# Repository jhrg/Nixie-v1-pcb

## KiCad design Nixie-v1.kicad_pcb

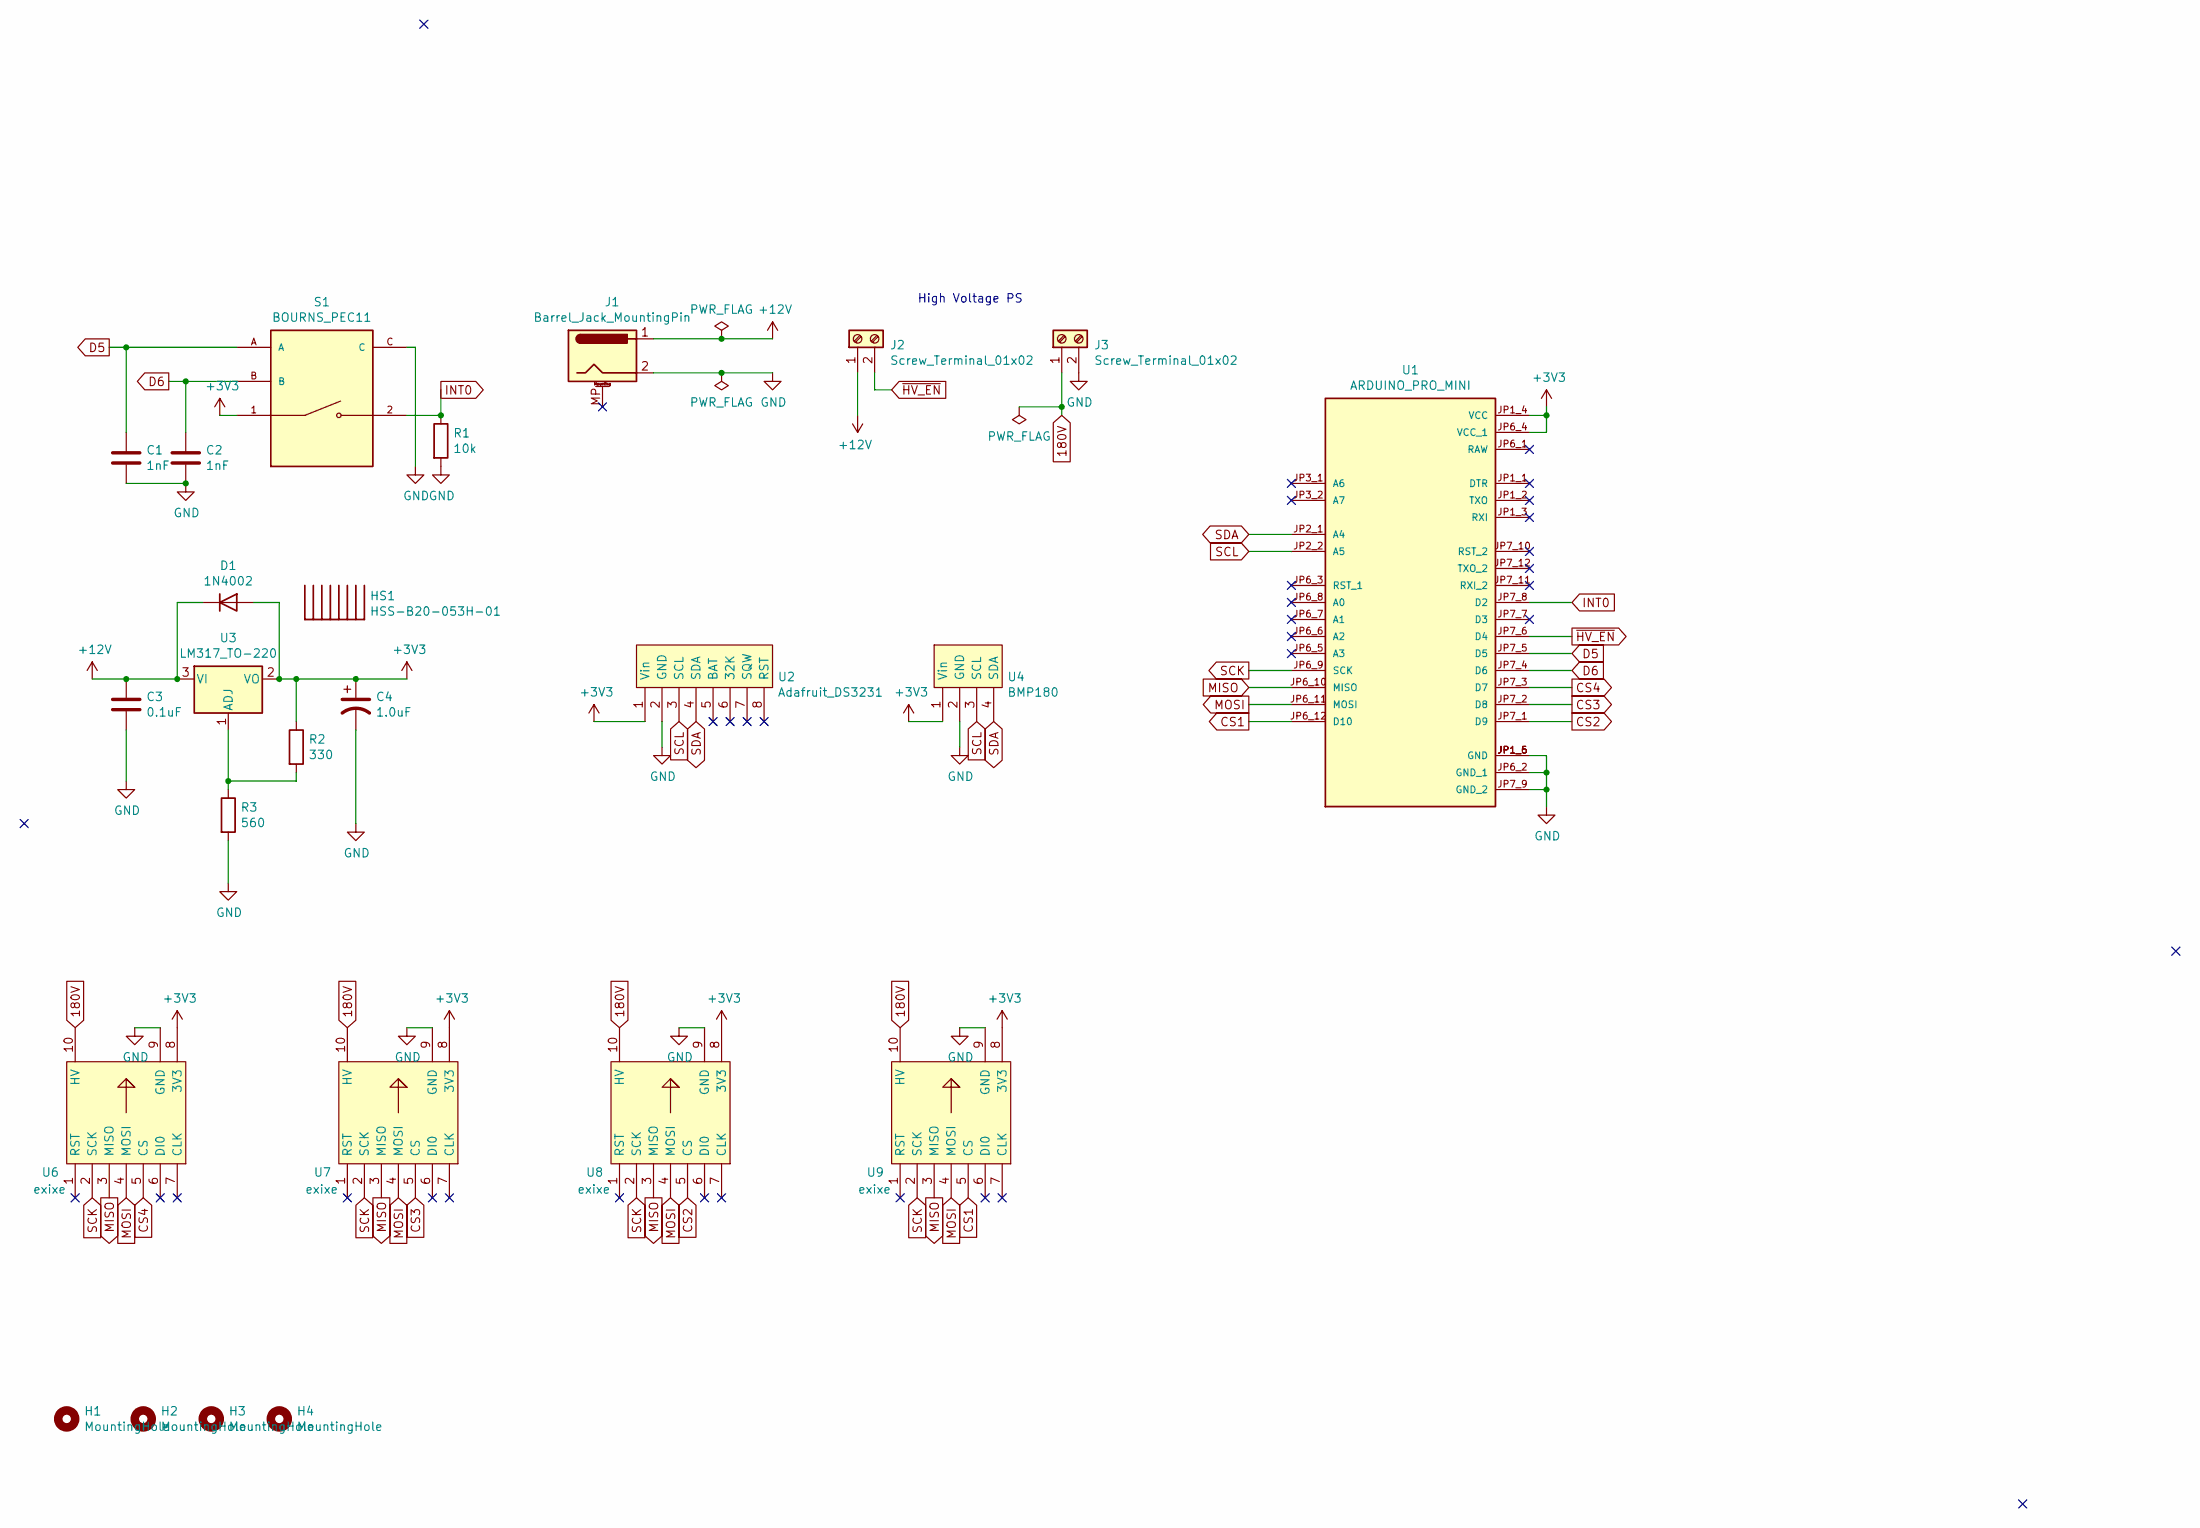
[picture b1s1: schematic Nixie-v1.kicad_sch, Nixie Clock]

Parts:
C1, C2: 1nF; C_Disc_D5.0mm_W2.5mm_P5.00mm
C3: 0.1uF; C_Rect_L11.0mm_W4.2mm_P10.00mm_MKT
C4: 1.0uF; CP_Radial_D10.0mm_P7.50mm
D1: 1N4002; D_DO-41_SOD81_P7.62mm_Horizontal
H1, H2, H3, H4: MountingHole; MountingHole_2.2mm_M2
HS1: HSS-B20-053H-01; HSINK_HSS-B20-053H-01
J1: Barrel_Jack_MountingPin; BarrelJack_Horizontal_MP
J2, J3: Screw_Terminal_01x02; TerminalBlock_RND_205-00001_1x02_P5.00mm_Horizontal
R1: 10k; R_Axial_DIN0207_L6.3mm_D2.5mm_P10.16mm_Horizontal
R2: 330; R_Axial_DIN0207_L6.3mm_D2.5mm_P10.16mm_Horizontal
R3: 560; R_Axial_DIN0207_L6.3mm_D2.5mm_P10.16mm_Horizontal
S1: BOURNS_PEC11; BOURNS-PEC11
U1: ARDUINO_PRO_MINI; MODULE_ARDUINO_PRO_MINI; PARTREV N/A
U2: Adafruit_DS3231; Adafruit_DS3231_bb
U3: LM317_TO-220; TO-220-3_Vertical
U4: BMP180; BMP180_bb
U6, U7, U8, U9: exixe; exixe-IN-14N

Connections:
180V: J3.1, U6.10 (HV), U7.10 (HV), U8.10 (HV), U9.10 (HV)
+3V3: C4.1, D1.2 (A), R2.1, S1.1, U1.JP1_4 (VCC), U1.JP6_4 (VCC_1), U2.1 (Vin), U3.2 (VO), U4.1 (Vin), U6.8 (3V3), U7.8 (3V3), U8.8 (3V3), U9.8 (3V3)
+12V: C3.1, D1.1 (K), J1.1, J2.1, U3.3 (VI)
CS1: U1.JP6_12 (D10), U9.5 (CS)
CS2: U1.JP7_1 (D9), U8.5 (CS)
CS3: U1.JP7_2 (D8), U7.5 (CS)
CS4: U1.JP7_3 (D7), U6.5 (CS)
D5: C1.1, S1.A, U1.JP7_5 (D5)
D6: C2.1, S1.B, U1.JP7_4 (D6)
GND: C1.2, C2.2, C3.2, C4.2, J1.2, J3.2, R1.2, R3.2, S1.C, U1.JP1_5 (GND), U1.JP1_6 (GND), U1.JP6_2 (GND_1), U1.JP7_9 (GND_2), U2.2 (GND), U4.2 (GND), U6.9 (GND), U7.9 (GND), U8.9 (GND), U9.9 (GND)
INT0: R1.1, S1.2, U1.JP7_8 (D2)
MISO: U1.JP6_10 (MISO), U6.3 (MISO), U7.3 (MISO), U8.3 (MISO), U9.3 (MISO)
MOSI: U1.JP6_11 (MOSI), U6.4 (MOSI), U7.4 (MOSI), U8.4 (MOSI), U9.4 (MOSI)
unnamed: HS1.1, HS1.2
unnamed: R2.2, R3.1, U3.1 (ADJ)
SCK: U1.JP6_9 (SCK), U6.2 (SCK), U7.2 (SCK), U8.2 (SCK), U9.2 (SCK)
SCL: U1.JP2_2 (A5), U2.3 (SCL), U4.3 (SCL)
SDA: U1.JP2_1 (A4), U2.4 (SDA), U4.4 (SDA)
~HV_EN: J2.2, U1.JP7_6 (D4)

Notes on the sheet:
High Voltage PS

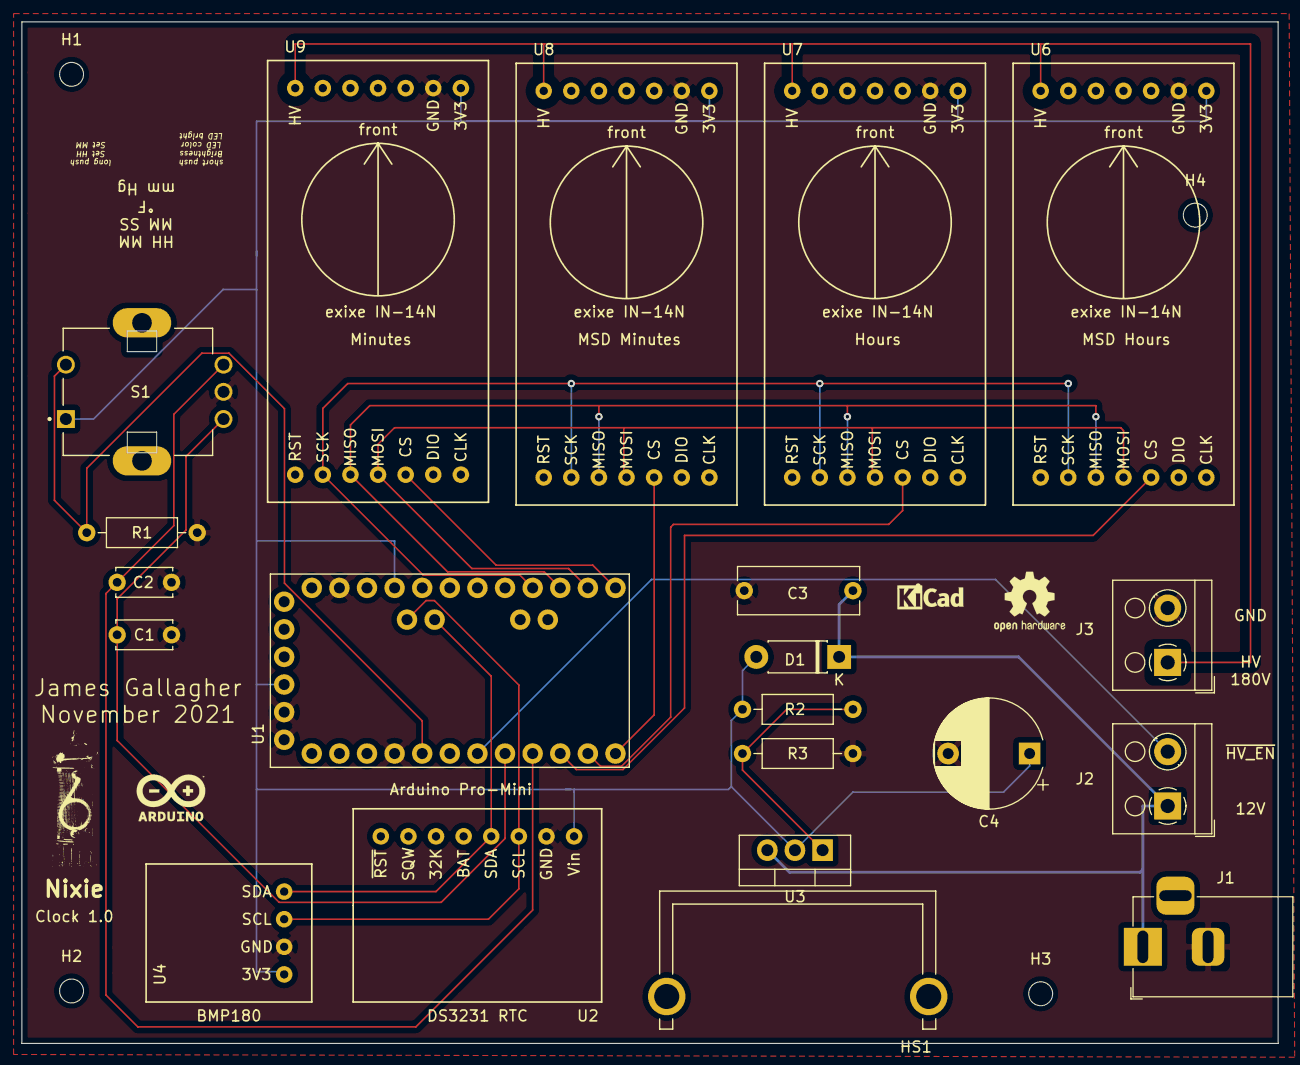
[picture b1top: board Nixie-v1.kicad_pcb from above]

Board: 2 copper layers, 115.5 x 93.9 mm, 25 parts (0 on the bottom side), 19 nets.

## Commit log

2023-03-06 Added files after downloading them from the iCloud directory

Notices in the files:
Nixie-v1.kicad_pcb:
https://creativecommons.org/licenses/by/4.0
CC by 4.0
